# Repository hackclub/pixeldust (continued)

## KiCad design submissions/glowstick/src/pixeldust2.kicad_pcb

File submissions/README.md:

Board-name: Neopixel-Audio-Wave

Slack-id: 0266FRGM

Wokwi: "https://wokwi.com/projects/426974431621216257"

This board uses an electret condenser microphone to gather audio data and 45 LEDs in a 5 x 9 grid. Each column is drawn based on the level of noise to form a waveform

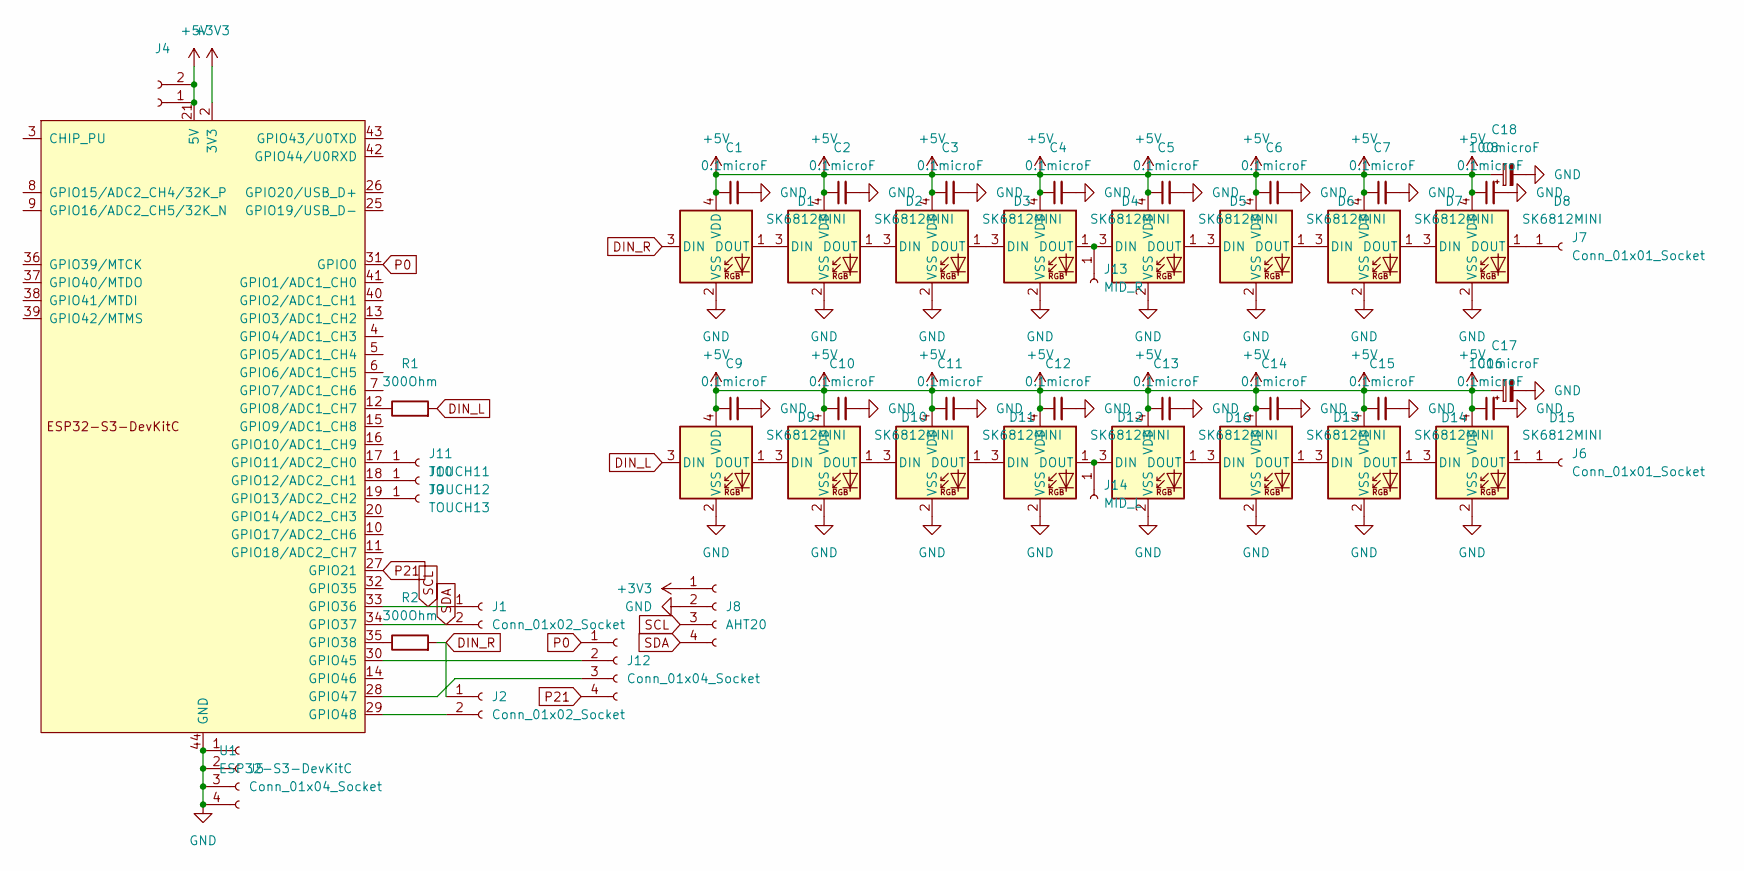
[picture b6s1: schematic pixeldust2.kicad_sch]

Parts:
C1, C2, C3, C4, C5, C6, C7, C8, C9, C10, C11, C12, C13, C14, C15, C16: 0.1microF; C_1206_3216Metric_Pad1.33x1.80mm_HandSolder
C17, C18: 100microF; CP_Radial_D8.0mm_P3.50mm
D1, D2, D3, D4, D5, D6, D7, D8, D9, D10, D11, D12, D13, D14, D15, D16: SK6812MINI; LED_SK6812MINI_PLCC4_3.5x3.5mm_P1.75mm
J1, J2, J4: Conn_01x02_Socket; PinSocket_1x02_P2.54mm_Vertical
J5, J12: Conn_01x04_Socket; PinSocket_1x04_P2.54mm_Vertical
J6, J7: Conn_01x01_Socket; PinSocket_1x01_P2.54mm_Vertical
J8: AHT20; Adafruit_AHT20
J9: TOUCH13; TOUCH
J10: TOUCH12; TOUCH
J11: TOUCH11; TOUCH
J13: MID_R; PinSocket_1x01_P1.27mm_Vertical
J14: MID_L; PinSocket_1x01_P1.27mm_Vertical
R1, R2: 300Ohm; R_Axial_DIN0207_L6.3mm_D2.5mm_P10.16mm_Horizontal
U1: ESP32-S3-DevKitC

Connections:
+3V3: J8.1, U1.1 (3V3), U1.2 (3V3)
+5V: C1.1, C2.1, C3.1, C4.1, C5.1, C6.1, C7.1, C8.1, C9.1, C10.1, C11.1, C12.1, C13.1, C14.1, C15.1, C16.1, C17.1, C18.1, D1.4 (VDD), D2.4 (VDD), D3.4 (VDD), D4.4 (VDD), D5.4 (VDD), D6.4 (VDD), D7.4 (VDD), D8.4 (VDD), D9.4 (VDD), D10.4 (VDD), D11.4 (VDD), D12.4 (VDD), D13.4 (VDD), D14.4 (VDD), D15.4 (VDD), D16.4 (VDD), J4.1, J4.2, U1.21 (5V)
DIN_L: D9.3 (DIN), R1.2
DIN_R: D1.3 (DIN), J2.1, R2.2
GND: C1.2, C2.2, C3.2, C4.2, C5.2, C6.2, C7.2, C8.2, C9.2, C10.2, C11.2, C12.2, C13.2, C14.2, C15.2, C16.2, C17.2, C18.2, D1.2 (VSS), D2.2 (VSS), D3.2 (VSS), D4.2 (VSS), D5.2 (VSS), D6.2 (VSS), D7.2 (VSS), D8.2 (VSS), D9.2 (VSS), D10.2 (VSS), D11.2 (VSS), D12.2 (VSS), D13.2 (VSS), D14.2 (VSS), D15.2 (VSS), D16.2 (VSS), J5.1, J5.2, J5.3, J5.4, J8.2, U1.22 (GND), U1.23 (GND), U1.24 (GND), U1.44 (GND)
unnamed: D1.1 (DOUT), D2.3 (DIN)
unnamed: D2.1 (DOUT), D3.3 (DIN)
unnamed: D3.1 (DOUT), D4.3 (DIN)
unnamed: D4.1 (DOUT), D5.3 (DIN), J13.1
unnamed: D5.1 (DOUT), D6.3 (DIN)
unnamed: D6.1 (DOUT), D7.3 (DIN)
unnamed: D7.1 (DOUT), D8.3 (DIN)
unnamed: D8.1 (DOUT), J7.1
unnamed: D9.1 (DOUT), D10.3 (DIN)
unnamed: D10.1 (DOUT), D11.3 (DIN)
unnamed: D11.1 (DOUT), D12.3 (DIN)
unnamed: D12.1 (DOUT), D16.3 (DIN), J14.1
unnamed: D13.3 (DIN), D16.1 (DOUT)
unnamed: D13.1 (DOUT), D14.3 (DIN)
unnamed: D14.1 (DOUT), D15.3 (DIN)
unnamed: D15.1 (DOUT), J6.1
unnamed: J2.2, U1.29 (GPIO48)
unnamed: J9.1, U1.19 (GPIO13/ADC2_CH2)
unnamed: J10.1, U1.18 (GPIO12/ADC2_CH1)
unnamed: J11.1, U1.17 (GPIO11/ADC2_CH0)
unnamed: J12.2, U1.30 (GPIO45)
unnamed: J12.3, U1.28 (GPIO47)
unnamed: R1.1, U1.12 (GPIO8/ADC1_CH7)
unnamed: R2.1, U1.35 (GPIO38)
P0: J12.1, U1.31 (GPIO0)
P21: J12.4, U1.27 (GPIO21)
SCL: J1.1, J8.3, U1.33 (GPIO36)
SDA: J1.2, J8.4, U1.34 (GPIO37)

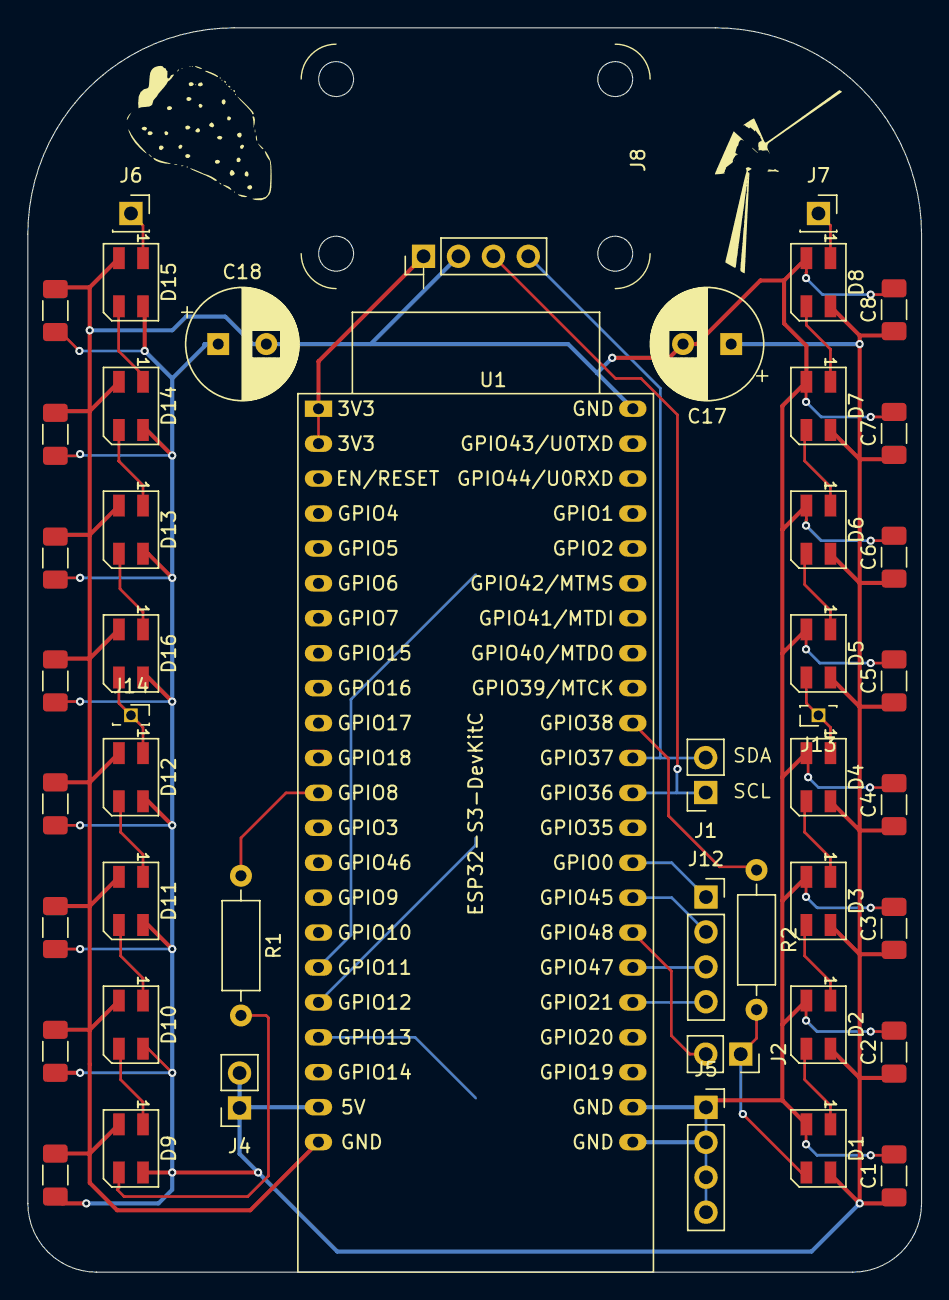
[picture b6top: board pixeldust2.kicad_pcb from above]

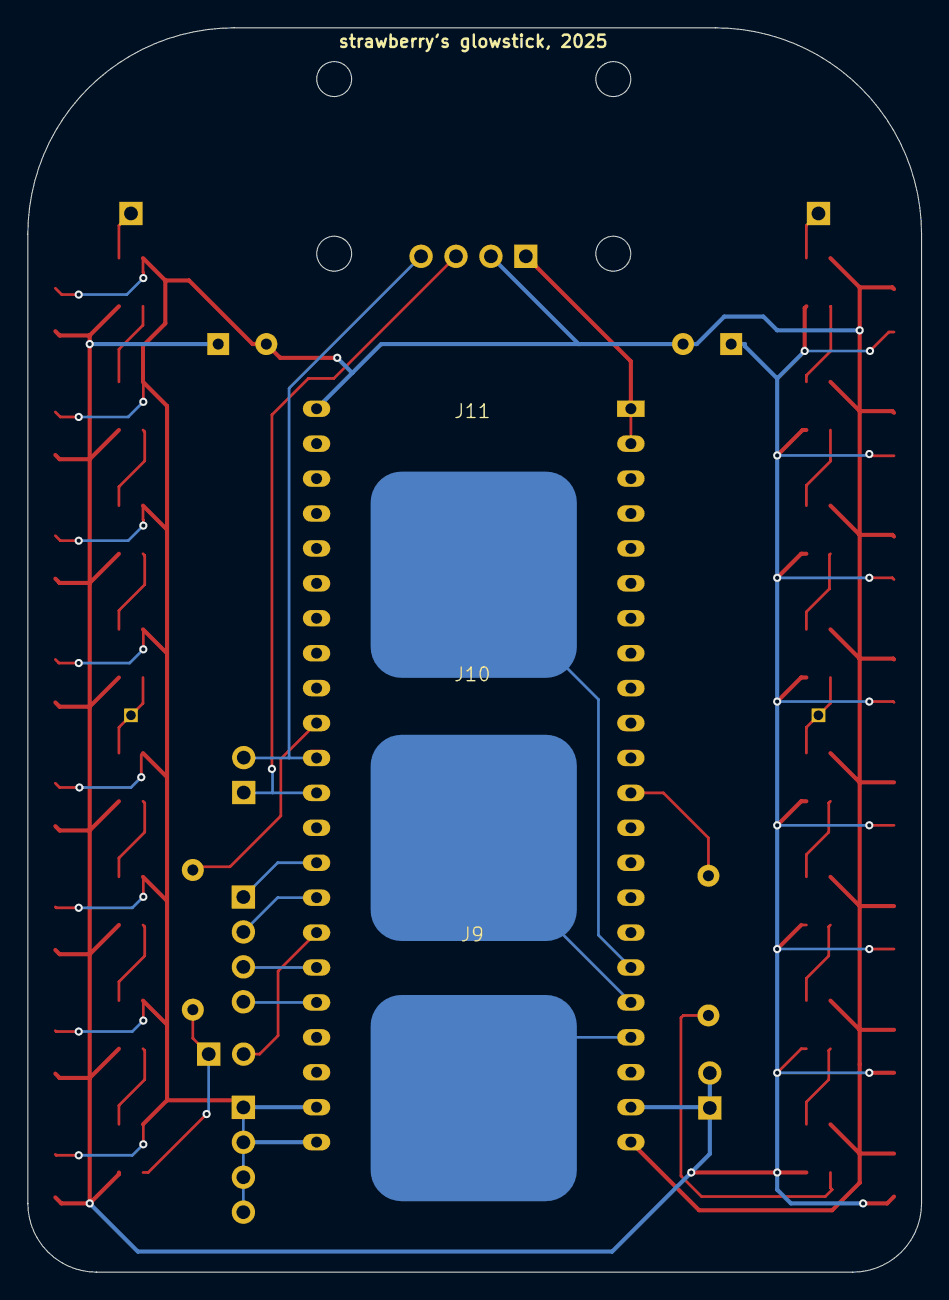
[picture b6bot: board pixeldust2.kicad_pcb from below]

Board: 2 copper layers, 65.0 x 90.5 mm, 50 parts (3 on the bottom side), 33 nets.

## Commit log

2025-03-31 Create hello
2025-04-14 lipoT
2025-04-14 added
2025-04-14 added pdf
2025-04-16 added photolux
2025-04-18 more info on submitting!
2025-05-01 fix filepaths
2025-05-01 renamed: submisssions/TheJSMatrix/BOM.csv -> submissions/TheJSMatrix/BOM.csv renamed: submisssions/TheJSMatrix/PCB.png -> submissions/TheJSMatrix/PCB.png renamed: submisssions/TheJSMatrix/README.md -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
2025-05-02 updated pixel-dongle and added gerbers (person20020)
2025-05-02 Update README.md -- fixed bom and added images
2025-05-02 Update README.md -- fixed number of neopixels
2025-05-03 readme + images
2025-05-03 final
2025-05-03 fix code + wokwi works now!
2025-05-04 updates for submission
2025-05-05 feat: add pxlboard
2025-05-05 feat: round corners
2025-05-05 feat: add power usbc
